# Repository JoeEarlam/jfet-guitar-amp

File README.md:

# jfet-guitar-amp

Headphone amplifier for guitars, using JFETs for smooth distortion and an op-amp to drive stereo headphones.

Uses "Fetzer Valve" stages for maximum gain and nominally valve-like distortion, with a big muff tone control arrangement.

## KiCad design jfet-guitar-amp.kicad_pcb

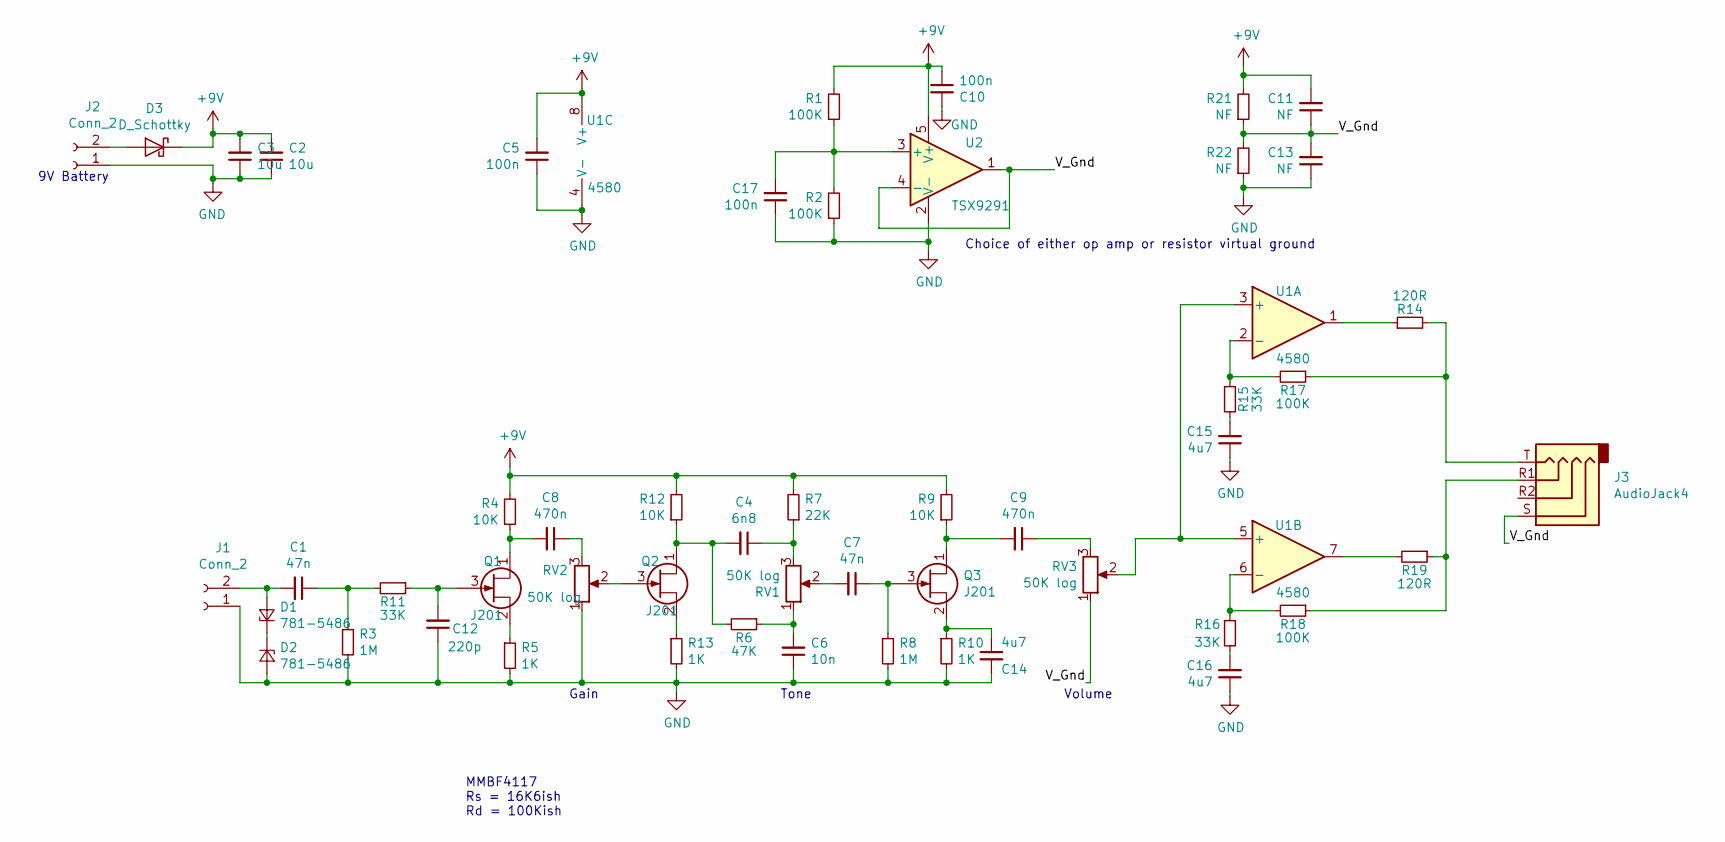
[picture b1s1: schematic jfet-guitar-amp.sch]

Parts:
C1, C7: 47n; C_0805_2012Metric
C2, C3: 10u; C_1206_3216Metric
C4: 6n8; C_0805_2012Metric
C5, C10, C17: 100n; C_0805_2012Metric
C6: 10n; C_0805_2012Metric
C8, C9: 470n; C_0805_2012Metric
C11, C13: NF; C_Elec_8x6.2
C12: 220p; C_0805_2012Metric
C14, C15, C16: 4u7; C_0805_2012Metric
D1, D2: 781-5486; D_SOT-23_ANK
D3: D_Schottky; D_SOD-123
J1, J2: Conn_2; wire_strainrelief_2
J3: AudioJack4; Jack_3.5mm_PJ320D_Horizontal
Q1, Q2, Q3: J201; SOT-23
R1, R2, R17, R18: 100K; R_0805_2012Metric
R3, R8: 1M; R_0805_2012Metric
R4, R9, R12: 10K; R_0805_2012Metric
R5, R10, R13: 1K; R_0805_2012Metric
R6: 47K; R_0805_2012Metric
R7: 22K; R_0805_2012Metric
R11, R15, R16: 33K; R_0805_2012Metric
R14, R19: 120R; R_0805_2012Metric
R21, R22: NF; R_0805_2012Metric
RV1, RV2, RV3: 50K log; Potentiometer_Alps_RK097_Single_Horizontal
U1: 4580; SOIC-8_3.9x4.9mm_P1.27mm
U2: TSX9291; SOT-23-5

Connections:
+9V: C2.2, C3.2, C5.2, C10.1, C11.2, D3.1 (K), R1.2, R4.2, R7.2, R9.2, R12.2, R21.2, U1.8 (V+), U2.5 (V+)
/V_Gnd: C11.1, C13.2, J3.S, R21.1, R22.2, RV3.1, U2.1, U2.4 (-)
GND: C2.1, C3.1, C5.1, C6.1, C10.2, C12.1, C13.1, C14.2, C15.1, C16.1, C17.1, D2.2 (A), J1.1, J2.1, R2.1, R3.2, R5.2, R8.2, R10.2, R13.2, R22.1, RV2.1, U1.4 (V-), U2.2 (V-)
unnamed: C1.1, R3.1, R11.2
unnamed: C1.2, D1.2 (A), J1.2
unnamed: C4.1, R7.1, RV1.3
unnamed: C4.2, Q2.1 (D), R6.2, R12.1
unnamed: C6.2, R6.1, RV1.1
unnamed: C7.1, Q3.3 (G), R8.1
unnamed: C7.2, RV1.2
unnamed: C8.1, RV2.3
unnamed: C8.2, Q1.1 (D), R4.1
unnamed: C9.1, RV3.3
unnamed: C9.2, Q3.1 (D), R9.1
unnamed: C12.2, Q1.3 (G), R11.1
unnamed: C14.1, Q3.2 (S), R10.1
unnamed: C15.2, R15.2
unnamed: C16.2, R16.2
unnamed: C17.2, R1.1, R2.2, U2.3 (+)
unnamed: D1.1 (K), D2.1 (K)
unnamed: D3.2 (A), J2.2
unnamed: J3.R1, R18.1, R19.1
unnamed: J3.T, R14.2, R17.1
unnamed: Q1.2 (S), R5.1
unnamed: Q2.2 (S), R13.1
unnamed: Q2.3 (G), RV2.2
unnamed: R14.1, U1.1
unnamed: R15.1, R17.2, U1.2 (-)
unnamed: R16.1, R18.2, U1.6 (-)
unnamed: R19.2, U1.7
unnamed: RV3.2, U1.3 (+), U1.5 (+)

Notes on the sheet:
Tone
Gain
9V Battery
Volume
MMBF4117 Rs = 16K6ish Rd = 100Kish
Choice of either op amp or resistor virtual ground

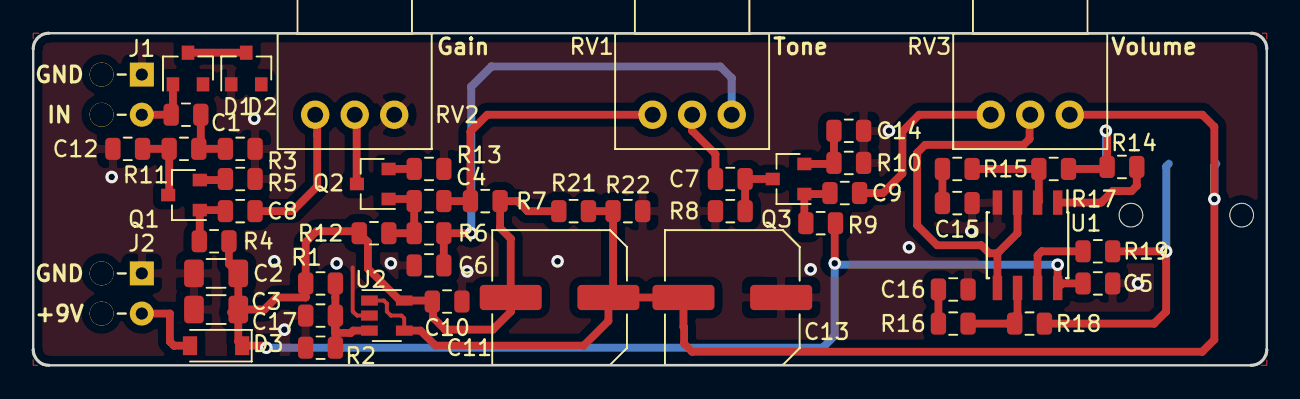
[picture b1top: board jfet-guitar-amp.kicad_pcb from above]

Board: 2 copper layers, 78.0 x 21.0 mm, 52 parts (1 on the bottom side), 31 nets.

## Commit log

2018-12-17 changes to component footprints, new layout WIP
2018-12-18 PCB updated
2019-01-09 minor component value changes
2019-01-21 added PCB mount headphone socket, minor component changes
2019-01-24 updated gitignore
2019-02-02 prepare to send to manufacture
2019-02-07 minor schematic changes to feedback loop and BOM, tag for prototype production
2019-02-10 as sent to production
2019-03-29 small tweaks: decoupling for split supply, tidied up schematic, moved via to reduce likelihood of ground loops
